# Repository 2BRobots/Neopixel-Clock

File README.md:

# Neopixel-Clock
You can find here the files for laser cutting, pcb's and other resources to build this proyect. The Neopixel clock. 
This is an open source proyect, Creative Commons licence.

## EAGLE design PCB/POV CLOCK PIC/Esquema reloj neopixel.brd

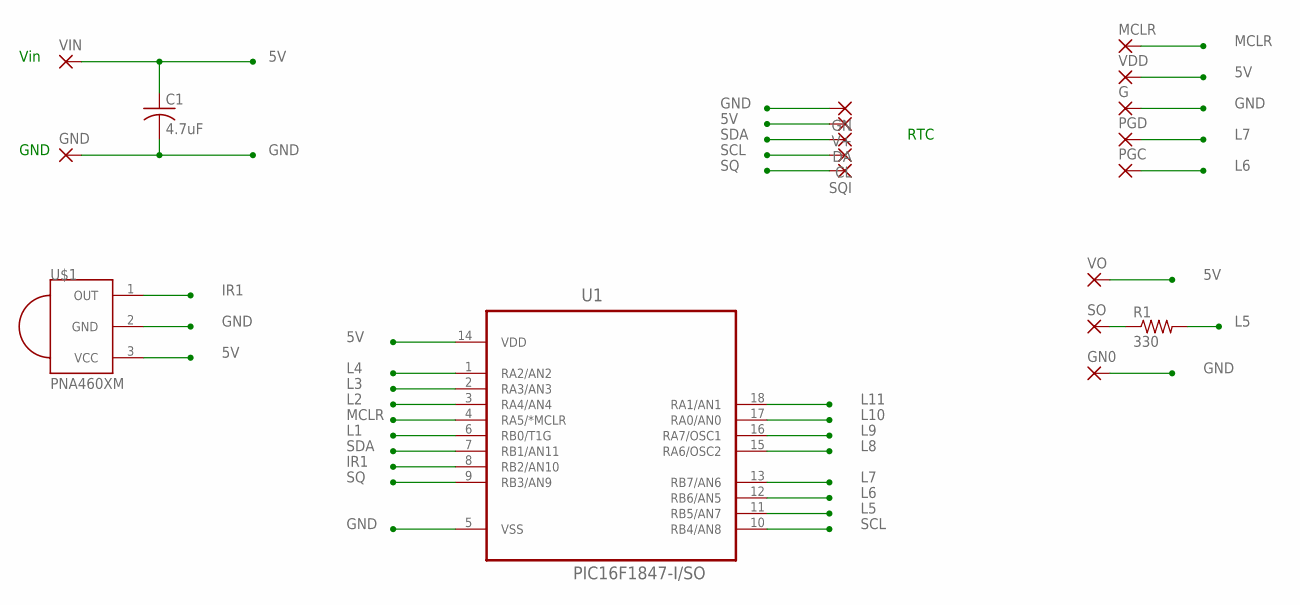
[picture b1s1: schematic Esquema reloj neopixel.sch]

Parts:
C1: 4.7uF; C0805K
CL: SMD2; SMD1,27-2,54
DA: SMD2; SMD1,27-2,54
G: SMD2; SMD1,27-2,54
GN, GN0: SMD2; SMD1,27-2,54
GND: SMD2; SMD1,27-2,54
MCLR: SMD2; SMD1,27-2,54
PGC: SMD2; SMD1,27-2,54
PGD: SMD2; SMD1,27-2,54
R1: 330; R0805
SO: SMD2; SMD1,27-2,54
SQI: SMD2; SMD1,27-2,54
U1: PIC16F1847-I/SO; SOIC127P1030X265-18N
U$1: PNA460XM
V+: SMD2; SMD1,27-2,54
VDD: SMD2; SMD1,27-2,54
VIN: SMD2; SMD1,27-2,54
VO: SMD2; SMD1,27-2,54

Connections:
5V: C1.1, U1.14 (VDD), U$1.3 (VCC), V+.1, VDD.1, VIN.1, VO.1
GND: C1.2, G.1, GN.1, GN0.1, GND.1, U1.5 (VSS), U$1.2 (GND)
IR1: U1.8 (RB2/AN10), U$1.1 (OUT)
L1: U1.6 (RB0/T1G)
L2: U1.3 (RA4/AN4)
L3: U1.2 (RA3/AN3)
L4: U1.1 (RA2/AN2)
L5: R1.2, U1.11 (RB5/AN7)
L6: PGC.1, U1.12 (RB6/AN5)
L7: PGD.1, U1.13 (RB7/AN6)
L8: U1.15 (RA6/OSC2)
L9: U1.16 (RA7/OSC1)
L10: U1.17 (RA0/AN0)
L11: U1.18 (RA1/AN1)
MCLR: MCLR.1, U1.4 (RA5/*MCLR)
unnamed: R1.1, SO.1
SCL: CL.1, U1.10 (RB4/AN8)
SDA: DA.1, U1.7 (RB1/AN11)
SQ: SQI.1, U1.9 (RB3/AN9)

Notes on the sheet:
Vin
GND
RTC

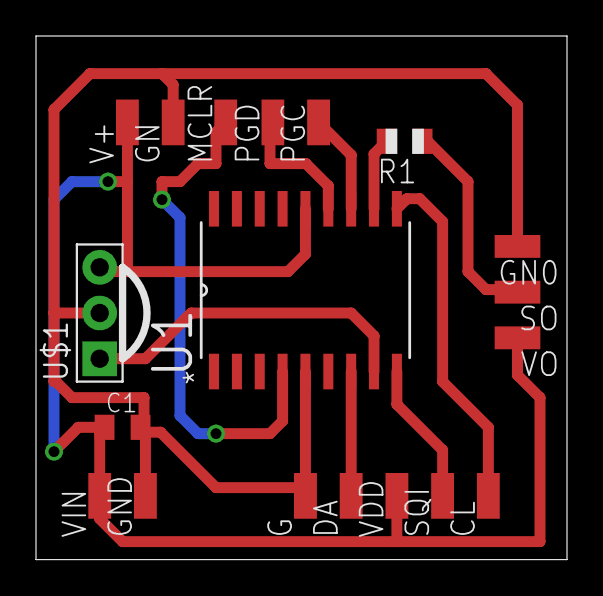
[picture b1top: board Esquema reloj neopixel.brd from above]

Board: 2 copper layers, 29.5 x 29.1 mm, 19 parts (0 on the bottom side), 11 nets.

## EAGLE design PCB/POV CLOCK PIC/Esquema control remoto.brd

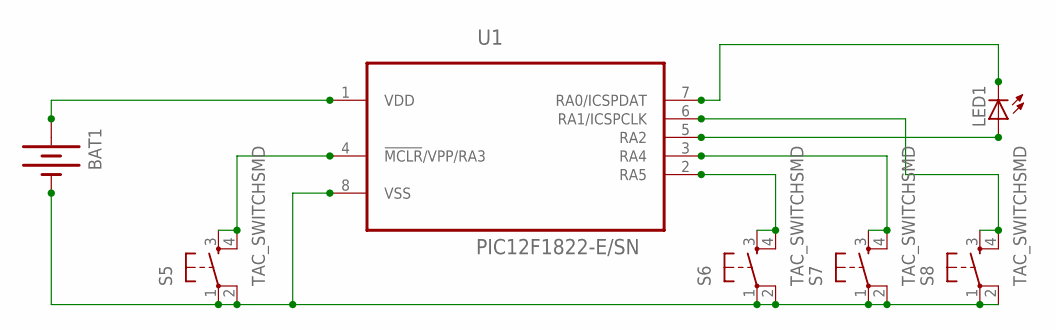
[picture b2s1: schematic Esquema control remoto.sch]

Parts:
BAT1: BATTERY20SMD; BATTCON_20MM
LED1: LEDCHIPLED_1206; CHIPLED_1206
S5, S6, S7, S8: TAC_SWITCHSMD; TACTILE-SWITCH-SMD
U1: PIC12F1822-E/SN; SOIC127P600X175-8N

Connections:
unnamed: LED1.C, U1.7 (RA0/ICSPDAT)
unnamed: LED1.A, U1.5 (RA2)
unnamed: S5.3, S5.4, U1.4 (!MCLR!/VPP/RA3)
unnamed: S6.3, S6.4, U1.2 (RA5)
unnamed: S7.3, S7.4, U1.3 (RA4)
unnamed: S8.3, S8.4, U1.6 (RA1/ICSPCLK)
unnamed: BAT1.2 (-), S5.1, S5.2, S6.1, S6.2, S7.1, S7.2, S8.1, S8.2, U1.8 (VSS)
unnamed: BAT1.1 (+), U1.1 (VDD)

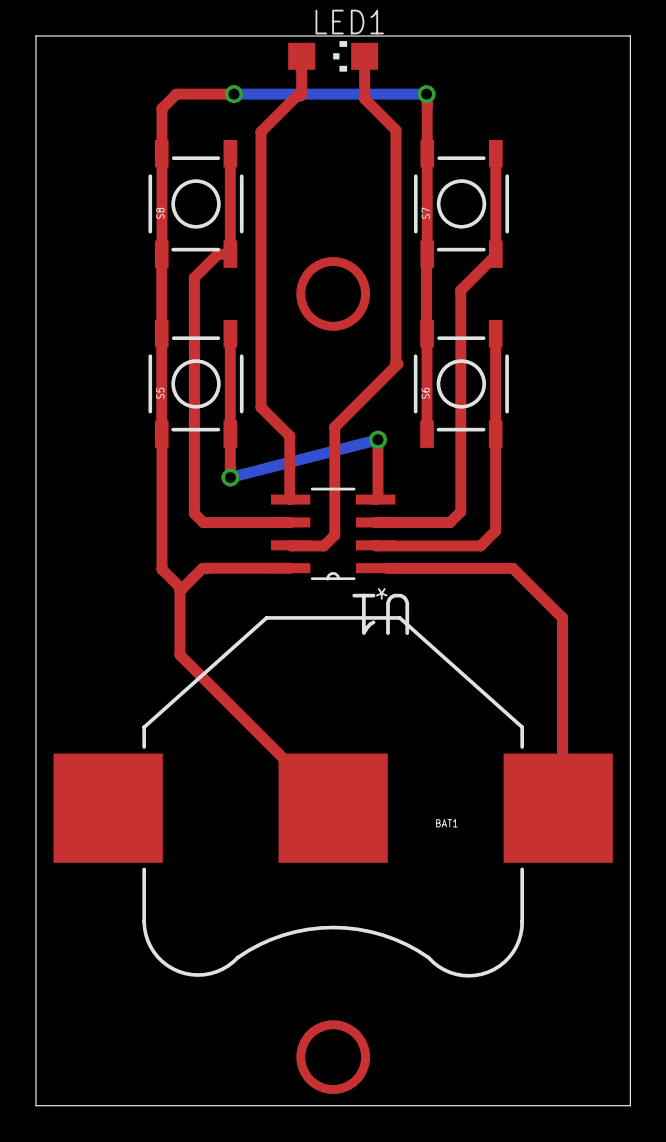
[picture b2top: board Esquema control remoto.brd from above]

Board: 2 copper layers, 33.0 x 59.4 mm, 7 parts (0 on the bottom side), 8 nets.

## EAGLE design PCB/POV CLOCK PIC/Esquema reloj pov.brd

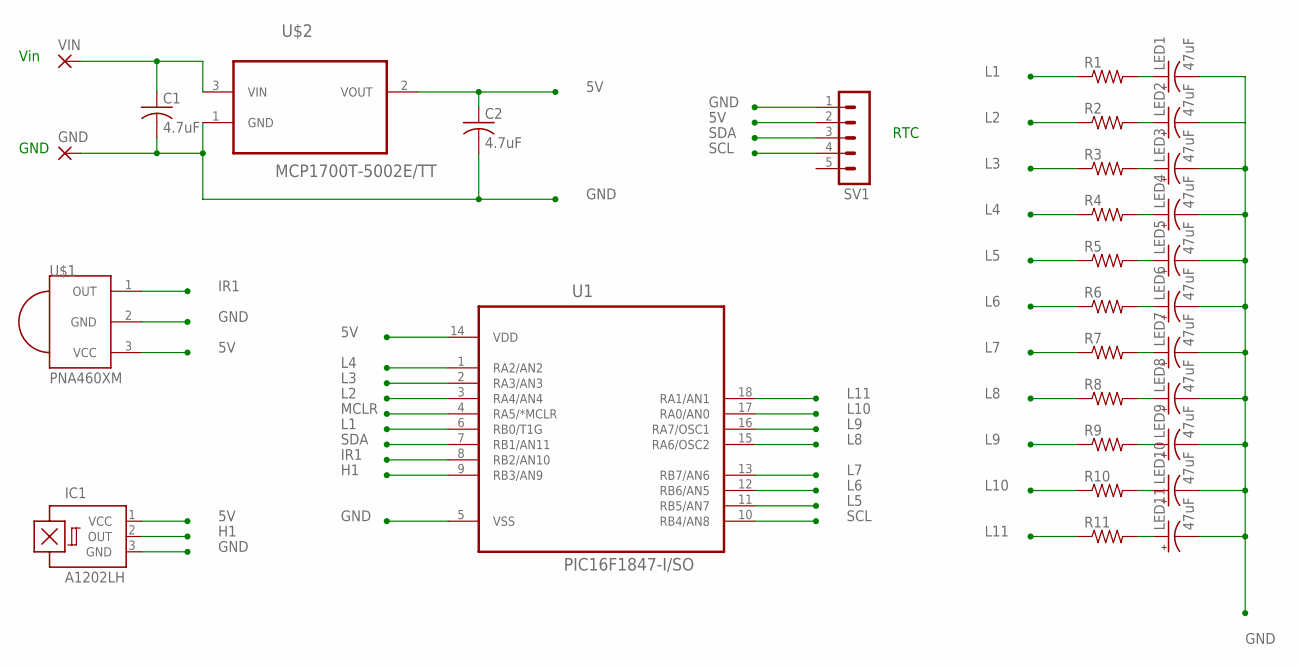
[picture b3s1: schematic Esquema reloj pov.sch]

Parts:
C1, C2: 4.7uF; C0805K
GND: 2,54/0,8
IC1: A1202LH; SOT23-W
LED1, LED2, LED3, LED4, LED5, LED6, LED7, LED8, LED9, LED10, LED11: 47uF; EIA3528
R1, R2, R3, R4, R5, R6, R7, R8, R9, R10, R11: R-US_R0805; R0805
SV1: MA05-1
U1: PIC16F1847-I/SO; SOIC127P1030X265-18N
U$1: PNA460XM
U$2: MCP1700T-5002E/TT; SOT95P237X112-3N
VIN: 2,54/0,8

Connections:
5V: C2.1, IC1.1 (VCC), SV1.2, U1.14 (VDD), U$1.3 (VCC), U$2.2 (VOUT)
GND: C1.2, C2.2, GND.1, IC1.3 (GND), LED1.C (-), LED2.C (-), LED3.C (-), LED4.C (-), LED5.C (-), LED6.C (-), LED7.C (-), LED8.C (-), LED9.C (-), LED10.C (-), LED11.C (-), SV1.1, U1.5 (VSS), U$1.2 (GND), U$2.1 (GND)
H1: IC1.2 (OUT), U1.9 (RB3/AN9)
IR1: U1.8 (RB2/AN10), U$1.1 (OUT)
L1: R1.1, U1.6 (RB0/T1G)
L2: R2.1, U1.3 (RA4/AN4)
L3: R3.1, U1.2 (RA3/AN3)
L4: R4.1, U1.1 (RA2/AN2)
L5: R5.1, U1.11 (RB5/AN7)
L6: R6.1, U1.12 (RB6/AN5)
L7: R7.1, U1.13 (RB7/AN6)
L8: R8.1, U1.15 (RA6/OSC2)
L9: R9.1, U1.16 (RA7/OSC1)
L10: R10.1, U1.17 (RA0/AN0)
L11: R11.1, U1.18 (RA1/AN1)
MCLR: U1.4 (RA5/*MCLR)
unnamed: LED1.A (+), R1.2
unnamed: C1.1, U$2.3 (VIN), VIN.1
unnamed: LED2.A (+), R2.2
unnamed: LED3.A (+), R3.2
unnamed: LED4.A (+), R4.2
unnamed: LED5.A (+), R5.2
unnamed: LED6.A (+), R6.2
unnamed: LED7.A (+), R7.2
unnamed: LED8.A (+), R8.2
unnamed: LED9.A (+), R9.2
unnamed: LED10.A (+), R10.2
unnamed: LED11.A (+), R11.2
SCL: SV1.4, U1.10 (RB4/AN8)
SDA: SV1.3, U1.7 (RB1/AN11)

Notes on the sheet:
Vin
GND
RTC

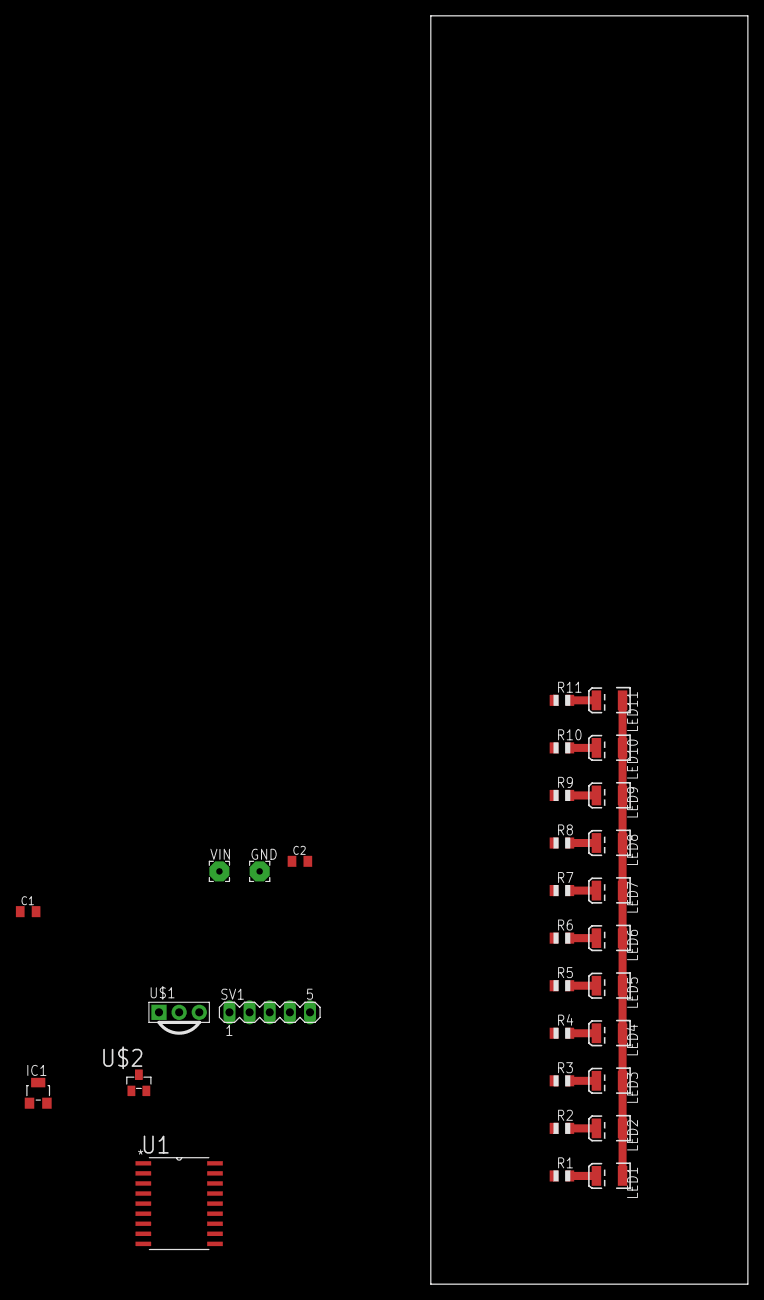
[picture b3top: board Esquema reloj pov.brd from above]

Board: 2 copper layers, 40.0 x 160.0 mm, 31 parts (0 on the bottom side), 29 nets.

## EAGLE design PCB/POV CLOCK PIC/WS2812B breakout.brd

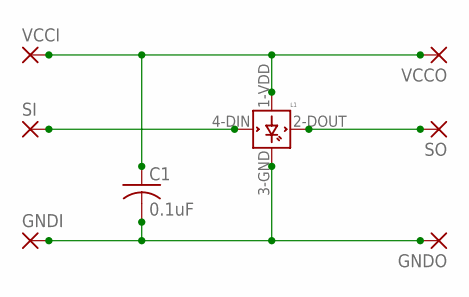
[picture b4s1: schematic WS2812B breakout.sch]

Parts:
C1: 0.1uF; C0402K
GNDI: SMD2; SMD1,27-2,54
GNDO: SMD2; SMD1,27-2,54
L1: WS2812B
SI: SMD2; SMD1,27-2,54
SO: SMD2; SMD1,27-2,54
VCCI: SMD2; SMD1,27-2,54
VCCO: SMD2; SMD1,27-2,54

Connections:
unnamed: C1.2, GNDI.1, GNDO.1, L1.3-GND (GND)
unnamed: C1.1, L1.1-VDD (VDD), VCCI.1, VCCO.1
unnamed: L1.4-DIN (DIN), SI.1
unnamed: L1.2-DOUT (DOUT), SO.1

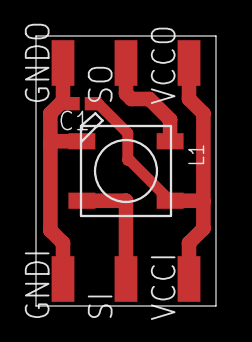
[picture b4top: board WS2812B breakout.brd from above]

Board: 2 copper layers, 10.0 x 15.0 mm, 8 parts (0 on the bottom side), 4 nets.

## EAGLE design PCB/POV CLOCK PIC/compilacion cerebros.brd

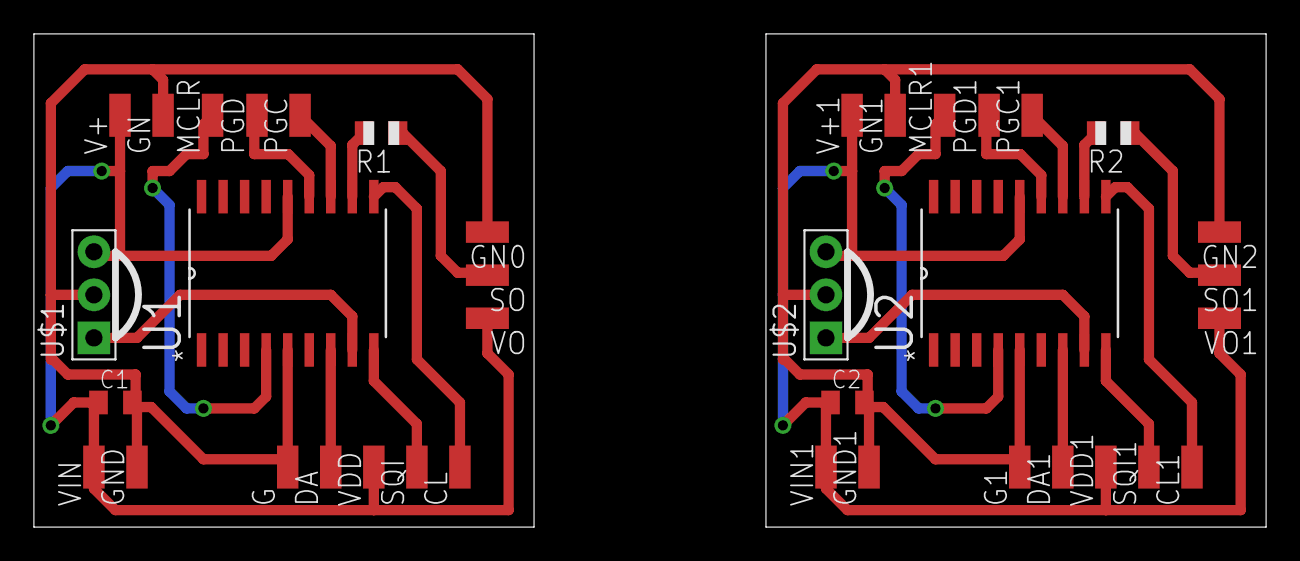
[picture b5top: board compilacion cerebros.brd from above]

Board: 2 copper layers, 72.7 x 29.1 mm, 38 parts (0 on the bottom side), 22 nets.

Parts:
C1, C2: 4.7uF; C0805K
CL, CL1: SMD1,27-2,54
DA, DA1: SMD1,27-2,54
G, G1: SMD1,27-2,54
GN, GN0, GN1, GN2: SMD1,27-2,54
GND, GND1: SMD1,27-2,54
MCLR, MCLR1: SMD1,27-2,54
PGC, PGC1: SMD1,27-2,54
PGD, PGD1: SMD1,27-2,54
R1, R2: 330; R0805
SO, SO1: SMD1,27-2,54
SQI, SQI1: SMD1,27-2,54
U1, U2: PIC16F1847-I/SO; SOIC127P1030X265-18N
U$1, U$2: PNA460XM
V+, V+1: SMD1,27-2,54
VDD, VDD1: SMD1,27-2,54
VIN, VIN1: SMD1,27-2,54
VO, VO1: SMD1,27-2,54

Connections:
5V: C1.1, U1.14, U$1.3, V+.1, VDD.1, VIN.1, VO.1
5V1: C2.1, U2.14, U$2.3, V+1.1, VDD1.1, VIN1.1, VO1.1
GND: C1.2, G.1, GN.1, GN0.1, GND.1, U1.5, U$1.2
GND1: C2.2, G1.1, GN1.1, GN2.1, GND1.1, U2.5, U$2.2
IR1: U1.8, U$1.1
IR2: U2.8, U$2.1
L5: R1.2, U1.11
L6: PGC.1, U1.12
L7: PGD.1, U1.13
L16: R2.2, U2.11
L17: PGC1.1, U2.12
L18: PGD1.1, U2.13
MCLR: MCLR.1, U1.4
MCLR1: MCLR1.1, U2.4
unnamed: R1.1, SO.1
unnamed: R2.1, SO1.1
SCL: CL.1, U1.10
SCL1: CL1.1, U2.10
SDA: DA.1, U1.7
SDA1: DA1.1, U2.7
SQ: SQI.1, U1.9
SQ1: SQI1.1, U2.9

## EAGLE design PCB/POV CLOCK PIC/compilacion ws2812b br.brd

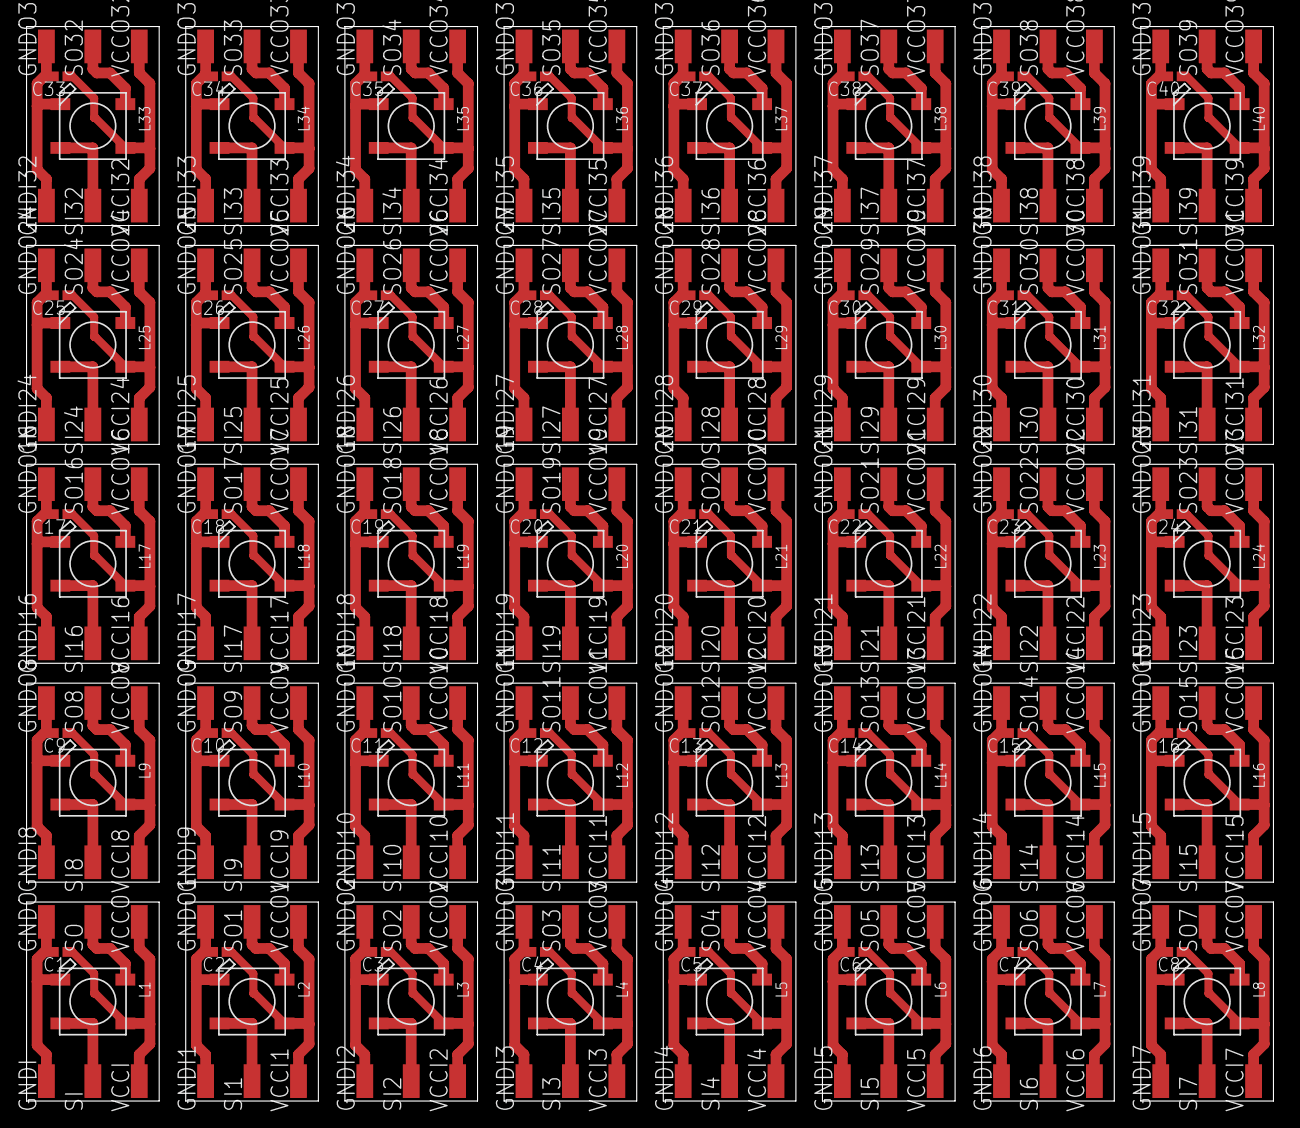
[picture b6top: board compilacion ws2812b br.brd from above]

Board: 2 copper layers, 94.0 x 81.0 mm, 320 parts (0 on the bottom side), 160 nets.

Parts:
C1, C2, C3, C4, C5, C6, C7, C8, C9, C10, C11, C12, C13, C14, C15, C16, C17, C18, C19, C20, C21, C22, C23, C24, C25, C26, C27, C28, C29, C30, C31, C32, C33, C34, C35, C36, C37, C38, C39, C40: 0.1uF; C0402K
GNDI, GNDI1, GNDI2, GNDI3, GNDI4, GNDI5, GNDI6, GNDI7, GNDI8, GNDI9, GNDI10, GNDI11, GNDI12, GNDI13, GNDI14, GNDI15, GNDI16, GNDI17, GNDI18, GNDI19, GNDI20, GNDI21, GNDI22, GNDI23, GNDI24, GNDI25, GNDI26, GNDI27, GNDI28, GNDI29, GNDI30, GNDI31, GNDI32, GNDI33, GNDI34, GNDI35, GNDI36, GNDI37, GNDI38, GNDI39: SMD1,27-2,54
GNDO, GNDO1, GNDO2, GNDO3, GNDO4, GNDO5, GNDO6, GNDO7, GNDO8, GNDO9, GNDO10, GNDO11, GNDO12, GNDO13, GNDO14, GNDO15, GNDO16, GNDO17, GNDO18, GNDO19, GNDO20, GNDO21, GNDO22, GNDO23, GNDO24, GNDO25, GNDO26, GNDO27, GNDO28, GNDO29, GNDO30, GNDO31, GNDO32, GNDO33, GNDO34, GNDO35, GNDO36, GNDO37, GNDO38, GNDO39: SMD1,27-2,54
L1, L2, L3, L4, L5, L6, L7, L8, L9, L10, L11, L12, L13, L14, L15, L16, L17, L18, L19, L20, L21, L22, L23, L24, L25, L26, L27, L28, L29, L30, L31, L32, L33, L34, L35, L36, L37, L38, L39, L40: WS2812B
SI, SI1, SI2, SI3, SI4, SI5, SI6, SI7, SI8, SI9, SI10, SI11, SI12, SI13, SI14, SI15, SI16, SI17, SI18, SI19, SI20, SI21, SI22, SI23, SI24, SI25, SI26, SI27, SI28, SI29, SI30, SI31, SI32, SI33, SI34, SI35, SI36, SI37, SI38, SI39: SMD1,27-2,54
SO, SO1, SO2, SO3, SO4, SO5, SO6, SO7, SO8, SO9, SO10, SO11, SO12, SO13, SO14, SO15, SO16, SO17, SO18, SO19, SO20, SO21, SO22, SO23, SO24, SO25, SO26, SO27, SO28, SO29, SO30, SO31, SO32, SO33, SO34, SO35, SO36, SO37, SO38, SO39: SMD1,27-2,54
VCCI, VCCI1, VCCI2, VCCI3, VCCI4, VCCI5, VCCI6, VCCI7, VCCI8, VCCI9, VCCI10, VCCI11, VCCI12, VCCI13, VCCI14, VCCI15, VCCI16, VCCI17, VCCI18, VCCI19, VCCI20, VCCI21, VCCI22, VCCI23, VCCI24, VCCI25, VCCI26, VCCI27, VCCI28, VCCI29, VCCI30, VCCI31, VCCI32, VCCI33, VCCI34, VCCI35, VCCI36, VCCI37, VCCI38, VCCI39: SMD1,27-2,54
VCCO, VCCO1, VCCO2, VCCO3, VCCO4, VCCO5, VCCO6, VCCO7, VCCO8, VCCO9, VCCO10, VCCO11, VCCO12, VCCO13, VCCO14, VCCO15, VCCO16, VCCO17, VCCO18, VCCO19, VCCO20, VCCO21, VCCO22, VCCO23, VCCO24, VCCO25, VCCO26, VCCO27, VCCO28, VCCO29, VCCO30, VCCO31, VCCO32, VCCO33, VCCO34, VCCO35, VCCO36, VCCO37, VCCO38, VCCO39: SMD1,27-2,54

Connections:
unnamed: C1.2, GNDI.1, GNDO.1, L1.3-GND
unnamed: C1.1, L1.1-VDD, VCCI.1, VCCO.1
unnamed: L1.4-DIN, SI.1
unnamed: L1.2-DOUT, SO.1
unnamed: C2.2, GNDI1.1, GNDO1.1, L2.3-GND
unnamed: C2.1, L2.1-VDD, VCCI1.1, VCCO1.1
unnamed: L2.4-DIN, SI1.1
unnamed: L2.2-DOUT, SO1.1
unnamed: C3.2, GNDI2.1, GNDO2.1, L3.3-GND
unnamed: C3.1, L3.1-VDD, VCCI2.1, VCCO2.1
unnamed: L3.4-DIN, SI2.1
unnamed: L3.2-DOUT, SO2.1
unnamed: C4.2, GNDI3.1, GNDO3.1, L4.3-GND
unnamed: C4.1, L4.1-VDD, VCCI3.1, VCCO3.1
unnamed: L4.4-DIN, SI3.1
unnamed: L4.2-DOUT, SO3.1
unnamed: C5.2, GNDI4.1, GNDO4.1, L5.3-GND
unnamed: C5.1, L5.1-VDD, VCCI4.1, VCCO4.1
unnamed: L5.4-DIN, SI4.1
unnamed: L5.2-DOUT, SO4.1
unnamed: C6.2, GNDI5.1, GNDO5.1, L6.3-GND
unnamed: C6.1, L6.1-VDD, VCCI5.1, VCCO5.1
unnamed: L6.4-DIN, SI5.1
unnamed: L6.2-DOUT, SO5.1
unnamed: C7.2, GNDI6.1, GNDO6.1, L7.3-GND
unnamed: C7.1, L7.1-VDD, VCCI6.1, VCCO6.1
unnamed: L7.4-DIN, SI6.1
unnamed: L7.2-DOUT, SO6.1
unnamed: C8.2, GNDI7.1, GNDO7.1, L8.3-GND
unnamed: C8.1, L8.1-VDD, VCCI7.1, VCCO7.1
unnamed: L8.4-DIN, SI7.1
unnamed: L8.2-DOUT, SO7.1
unnamed: C9.2, GNDI8.1, GNDO8.1, L9.3-GND
unnamed: C9.1, L9.1-VDD, VCCI8.1, VCCO8.1
unnamed: L9.4-DIN, SI8.1
unnamed: L9.2-DOUT, SO8.1
unnamed: C10.2, GNDI9.1, GNDO9.1, L10.3-GND
unnamed: C10.1, L10.1-VDD, VCCI9.1, VCCO9.1
unnamed: L10.4-DIN, SI9.1
unnamed: L10.2-DOUT, SO9.1
unnamed: C11.2, GNDI10.1, GNDO10.1, L11.3-GND
unnamed: C11.1, L11.1-VDD, VCCI10.1, VCCO10.1
unnamed: L11.4-DIN, SI10.1
unnamed: L11.2-DOUT, SO10.1
unnamed: C12.2, GNDI11.1, GNDO11.1, L12.3-GND
unnamed: C12.1, L12.1-VDD, VCCI11.1, VCCO11.1
unnamed: L12.4-DIN, SI11.1
unnamed: L12.2-DOUT, SO11.1
unnamed: C13.2, GNDI12.1, GNDO12.1, L13.3-GND
unnamed: C13.1, L13.1-VDD, VCCI12.1, VCCO12.1
unnamed: L13.4-DIN, SI12.1
unnamed: L13.2-DOUT, SO12.1
unnamed: C14.2, GNDI13.1, GNDO13.1, L14.3-GND
unnamed: C14.1, L14.1-VDD, VCCI13.1, VCCO13.1
unnamed: L14.4-DIN, SI13.1
unnamed: L14.2-DOUT, SO13.1
unnamed: C15.2, GNDI14.1, GNDO14.1, L15.3-GND
unnamed: C15.1, L15.1-VDD, VCCI14.1, VCCO14.1
unnamed: L15.4-DIN, SI14.1
unnamed: L15.2-DOUT, SO14.1
unnamed: C16.2, GNDI15.1, GNDO15.1, L16.3-GND
unnamed: C16.1, L16.1-VDD, VCCI15.1, VCCO15.1
unnamed: L16.4-DIN, SI15.1
unnamed: L16.2-DOUT, SO15.1
unnamed: C17.2, GNDI16.1, GNDO16.1, L17.3-GND
unnamed: C17.1, L17.1-VDD, VCCI16.1, VCCO16.1
unnamed: L17.4-DIN, SI16.1
unnamed: L17.2-DOUT, SO16.1
unnamed: C18.2, GNDI17.1, GNDO17.1, L18.3-GND
unnamed: C18.1, L18.1-VDD, VCCI17.1, VCCO17.1
unnamed: L18.4-DIN, SI17.1
unnamed: L18.2-DOUT, SO17.1
unnamed: C19.2, GNDI18.1, GNDO18.1, L19.3-GND
unnamed: C19.1, L19.1-VDD, VCCI18.1, VCCO18.1
unnamed: L19.4-DIN, SI18.1
unnamed: L19.2-DOUT, SO18.1
unnamed: C20.2, GNDI19.1, GNDO19.1, L20.3-GND
unnamed: C20.1, L20.1-VDD, VCCI19.1, VCCO19.1
unnamed: L20.4-DIN, SI19.1
unnamed: L20.2-DOUT, SO19.1
unnamed: C21.2, GNDI20.1, GNDO20.1, L21.3-GND
unnamed: C21.1, L21.1-VDD, VCCI20.1, VCCO20.1
unnamed: L21.4-DIN, SI20.1
unnamed: L21.2-DOUT, SO20.1
unnamed: C22.2, GNDI21.1, GNDO21.1, L22.3-GND
unnamed: C22.1, L22.1-VDD, VCCI21.1, VCCO21.1
unnamed: L22.4-DIN, SI21.1
unnamed: L22.2-DOUT, SO21.1
unnamed: C23.2, GNDI22.1, GNDO22.1, L23.3-GND
unnamed: C23.1, L23.1-VDD, VCCI22.1, VCCO22.1
unnamed: L23.4-DIN, SI22.1
unnamed: L23.2-DOUT, SO22.1
unnamed: C24.2, GNDI23.1, GNDO23.1, L24.3-GND
unnamed: C24.1, L24.1-VDD, VCCI23.1, VCCO23.1
unnamed: L24.4-DIN, SI23.1
unnamed: L24.2-DOUT, SO23.1
unnamed: C25.2, GNDI24.1, GNDO24.1, L25.3-GND
unnamed: C25.1, L25.1-VDD, VCCI24.1, VCCO24.1
unnamed: L25.4-DIN, SI24.1
unnamed: L25.2-DOUT, SO24.1
unnamed: C26.2, GNDI25.1, GNDO25.1, L26.3-GND
unnamed: C26.1, L26.1-VDD, VCCI25.1, VCCO25.1
unnamed: L26.4-DIN, SI25.1
unnamed: L26.2-DOUT, SO25.1
unnamed: C27.2, GNDI26.1, GNDO26.1, L27.3-GND
unnamed: C27.1, L27.1-VDD, VCCI26.1, VCCO26.1
unnamed: L27.4-DIN, SI26.1
unnamed: L27.2-DOUT, SO26.1
unnamed: C28.2, GNDI27.1, GNDO27.1, L28.3-GND
unnamed: C28.1, L28.1-VDD, VCCI27.1, VCCO27.1
unnamed: L28.4-DIN, SI27.1
unnamed: L28.2-DOUT, SO27.1
unnamed: C29.2, GNDI28.1, GNDO28.1, L29.3-GND
unnamed: C29.1, L29.1-VDD, VCCI28.1, VCCO28.1
unnamed: L29.4-DIN, SI28.1
unnamed: L29.2-DOUT, SO28.1
unnamed: C30.2, GNDI29.1, GNDO29.1, L30.3-GND
unnamed: C30.1, L30.1-VDD, VCCI29.1, VCCO29.1
unnamed: L30.4-DIN, SI29.1
unnamed: L30.2-DOUT, SO29.1
unnamed: C31.2, GNDI30.1, GNDO30.1, L31.3-GND
unnamed: C31.1, L31.1-VDD, VCCI30.1, VCCO30.1
unnamed: L31.4-DIN, SI30.1
unnamed: L31.2-DOUT, SO30.1
unnamed: C32.2, GNDI31.1, GNDO31.1, L32.3-GND
unnamed: C32.1, L32.1-VDD, VCCI31.1, VCCO31.1
unnamed: L32.4-DIN, SI31.1
unnamed: L32.2-DOUT, SO31.1
unnamed: C33.2, GNDI32.1, GNDO32.1, L33.3-GND
unnamed: C33.1, L33.1-VDD, VCCI32.1, VCCO32.1
unnamed: L33.4-DIN, SI32.1
unnamed: L33.2-DOUT, SO32.1
unnamed: C34.2, GNDI33.1, GNDO33.1, L34.3-GND
unnamed: C34.1, L34.1-VDD, VCCI33.1, VCCO33.1
unnamed: L34.4-DIN, SI33.1
unnamed: L34.2-DOUT, SO33.1
unnamed: C35.2, GNDI34.1, GNDO34.1, L35.3-GND
unnamed: C35.1, L35.1-VDD, VCCI34.1, VCCO34.1
unnamed: L35.4-DIN, SI34.1
unnamed: L35.2-DOUT, SO34.1
unnamed: C36.2, GNDI35.1, GNDO35.1, L36.3-GND
unnamed: C36.1, L36.1-VDD, VCCI35.1, VCCO35.1
unnamed: L36.4-DIN, SI35.1
unnamed: L36.2-DOUT, SO35.1
unnamed: C37.2, GNDI36.1, GNDO36.1, L37.3-GND
unnamed: C37.1, L37.1-VDD, VCCI36.1, VCCO36.1
unnamed: L37.4-DIN, SI36.1
unnamed: L37.2-DOUT, SO36.1
unnamed: C38.2, GNDI37.1, GNDO37.1, L38.3-GND
unnamed: C38.1, L38.1-VDD, VCCI37.1, VCCO37.1
unnamed: L38.4-DIN, SI37.1
unnamed: L38.2-DOUT, SO37.1
unnamed: C39.2, GNDI38.1, GNDO38.1, L39.3-GND
unnamed: C39.1, L39.1-VDD, VCCI38.1, VCCO38.1
unnamed: L39.4-DIN, SI38.1
unnamed: L39.2-DOUT, SO38.1
unnamed: C40.2, GNDI39.1, GNDO39.1, L40.3-GND
unnamed: C40.1, L40.1-VDD, VCCI39.1, VCCO39.1
unnamed: L40.4-DIN, SI39.1
unnamed: L40.2-DOUT, SO39.1

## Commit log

2015-11-23 1
    Firts version

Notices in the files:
parts and their libraries:
SparkFun-Electromechanical: Licensing: Creative Commons ShareAlike 4.0 International - https://creativecommons.org/licenses/by-sa/4.0
